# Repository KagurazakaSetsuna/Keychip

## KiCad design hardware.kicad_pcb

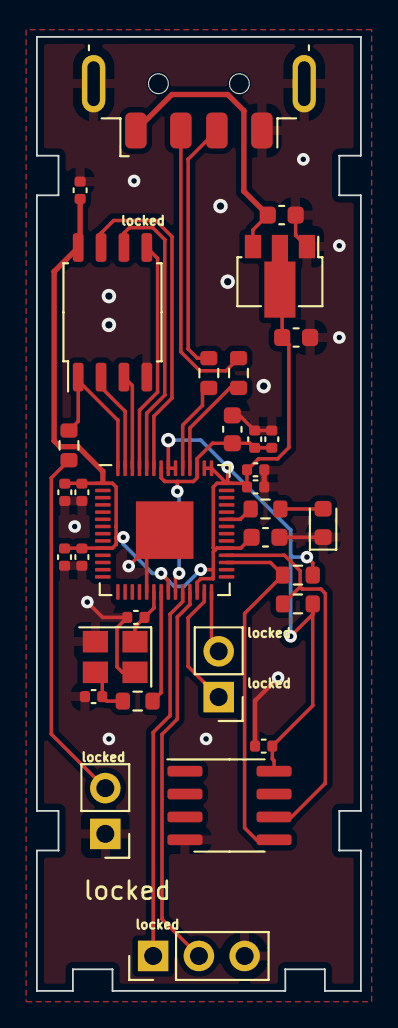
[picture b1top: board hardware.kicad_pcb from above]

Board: 2 copper layers, 18.0 x 53.0 mm, 33 parts (0 on the bottom side), 26 nets.

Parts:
C2, C4, C7, C8, C10, C11, C14, C17: 100n; C_0402_1005Metric
C9: 1u; C_0603_1608Metric
C12, C13: 10u; C_0603_1608Metric
C15, C16: 30p; C_0402_1005Metric
D1: LED; LED_0603_1608Metric
J1: USB_A; USB_A_Molex_48037-2200_Horizontal
J2, J4: Conn_01x02_Socket; PinHeader_1x02_P2.54mm_Vertical
J3: Conn_01x03_Pin; PinHeader_1x03_P2.54mm_Vertical
R1, R4: 1k; R_0603_1608Metric
R2, R3: 27.4; R_0603_1608Metric
R5: 470; R_0603_1608Metric
R6, R7: 4.7k; R_0603_1608Metric
U1: RP2040; QFN-56-1EP_7x7mm_P0.4mm_EP3.2x3.2mm
U3: W25Q80DV; SOIC-8_5.23x5.23mm_P1.27mm
U4: ATECC608A-SSHDA; SOIC-8_3.9x4.9mm_P1.27mm
U5: AMS1117-3.3; SOT-89-3
Y1: YSX321SL; Crystal_SMD_3225-4Pin_3.2x2.5mm
locked: 100n; C_0402_1005Metric
locked#2: 100n; C_0402_1005Metric
locked#3: 1u; C_0603_1608Metric

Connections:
+1V1: C9.1, C10.1, C11.1, U1.23 (DVDD), U1.45 (VREG_VOUT), U1.50 (DVDD)
+3V3: C2.1, C4.1, C7.1, C8.1, C13.1, C14.1, C17.1, R6.1, R7.2, U1.1 (IOVDD), U1.10 (IOVDD), U1.22 (IOVDD), U1.26 (RUN), U1.33 (IOVDD), U1.42 (IOVDD), U1.43 (ADC_AVDD), U1.44 (VREG_IN), U1.48 (USB_VDD), U1.49 (IOVDD), U3.8 (VCC), U4.8 (VCC), U5.2 (VO), locked.1, locked#2.1, locked#3.1
/DBG_RX: J4.2, U1.28 (GPIO17)
/DBG_TX: J4.1, U1.27 (GPIO16)
/LED: R5.1, U1.37 (GPIO25)
/QSPI_SCLK: U1.52 (QSPI_SCLK), U3.6 (CLK)
/QSPI_SD0: U1.53 (QSPI_SD0), U3.5 (DI(IO0))
/QSPI_SD1: U1.55 (QSPI_SD1), U3.2 (DO(IO1))
/QSPI_SD2: U1.54 (QSPI_SD2), U3.3 (IO2)
/QSPI_SD3: U1.51 (QSPI_SD3), U3.7 (IO3)
/QSPI_SS: R1.2, U1.56 (QSPI_SS), U3.1 (~CS)
/SCL: R6.2, U1.32 (GPIO21), U4.6 (SCL)
/SDA: R7.1, U1.31 (GPIO20), U4.5 (SDA)
/SWCLK: J3.1, U1.24 (SWCLK)
/SWDIO: J3.2, U1.25 (SWD)
/USB_D+: J1.3 (D+), R2.1
/USB_D-: J1.2 (D-), R3.1
/XIN: C16.1, U1.20 (XIN), Y1.1
/XOUT: C15.2, R4.1, Y1.3
/~BOOTSEL: J2.2, R1.1
GND: C2.2, C4.2, C7.2, C8.2, C9.2, C10.2, C11.2, C12.2, C13.2, C14.2, C15.1, C16.2, C17.2, D1.1 (K), J1.4 (GND), J1.5 (Shield), J2.1, J3.3, U1.19 (TESTEN), U1.57 (GND), U3.4 (GND), U4.4 (GND), U5.1 (GND), Y1.2, Y1.4, locked.2, locked#2.2, locked#3.2
unnamed: D1.2 (A), R5.2
unnamed: C12.1, J1.1 (VBUS), U5.3 (VI)
unnamed: R3.2, U1.46 (USB_DM)
unnamed: R2.2, U1.47 (USB_DP)
unnamed: R4.2, U1.21 (XOUT)

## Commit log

2023-11-11 Ver.HW1.00-R
